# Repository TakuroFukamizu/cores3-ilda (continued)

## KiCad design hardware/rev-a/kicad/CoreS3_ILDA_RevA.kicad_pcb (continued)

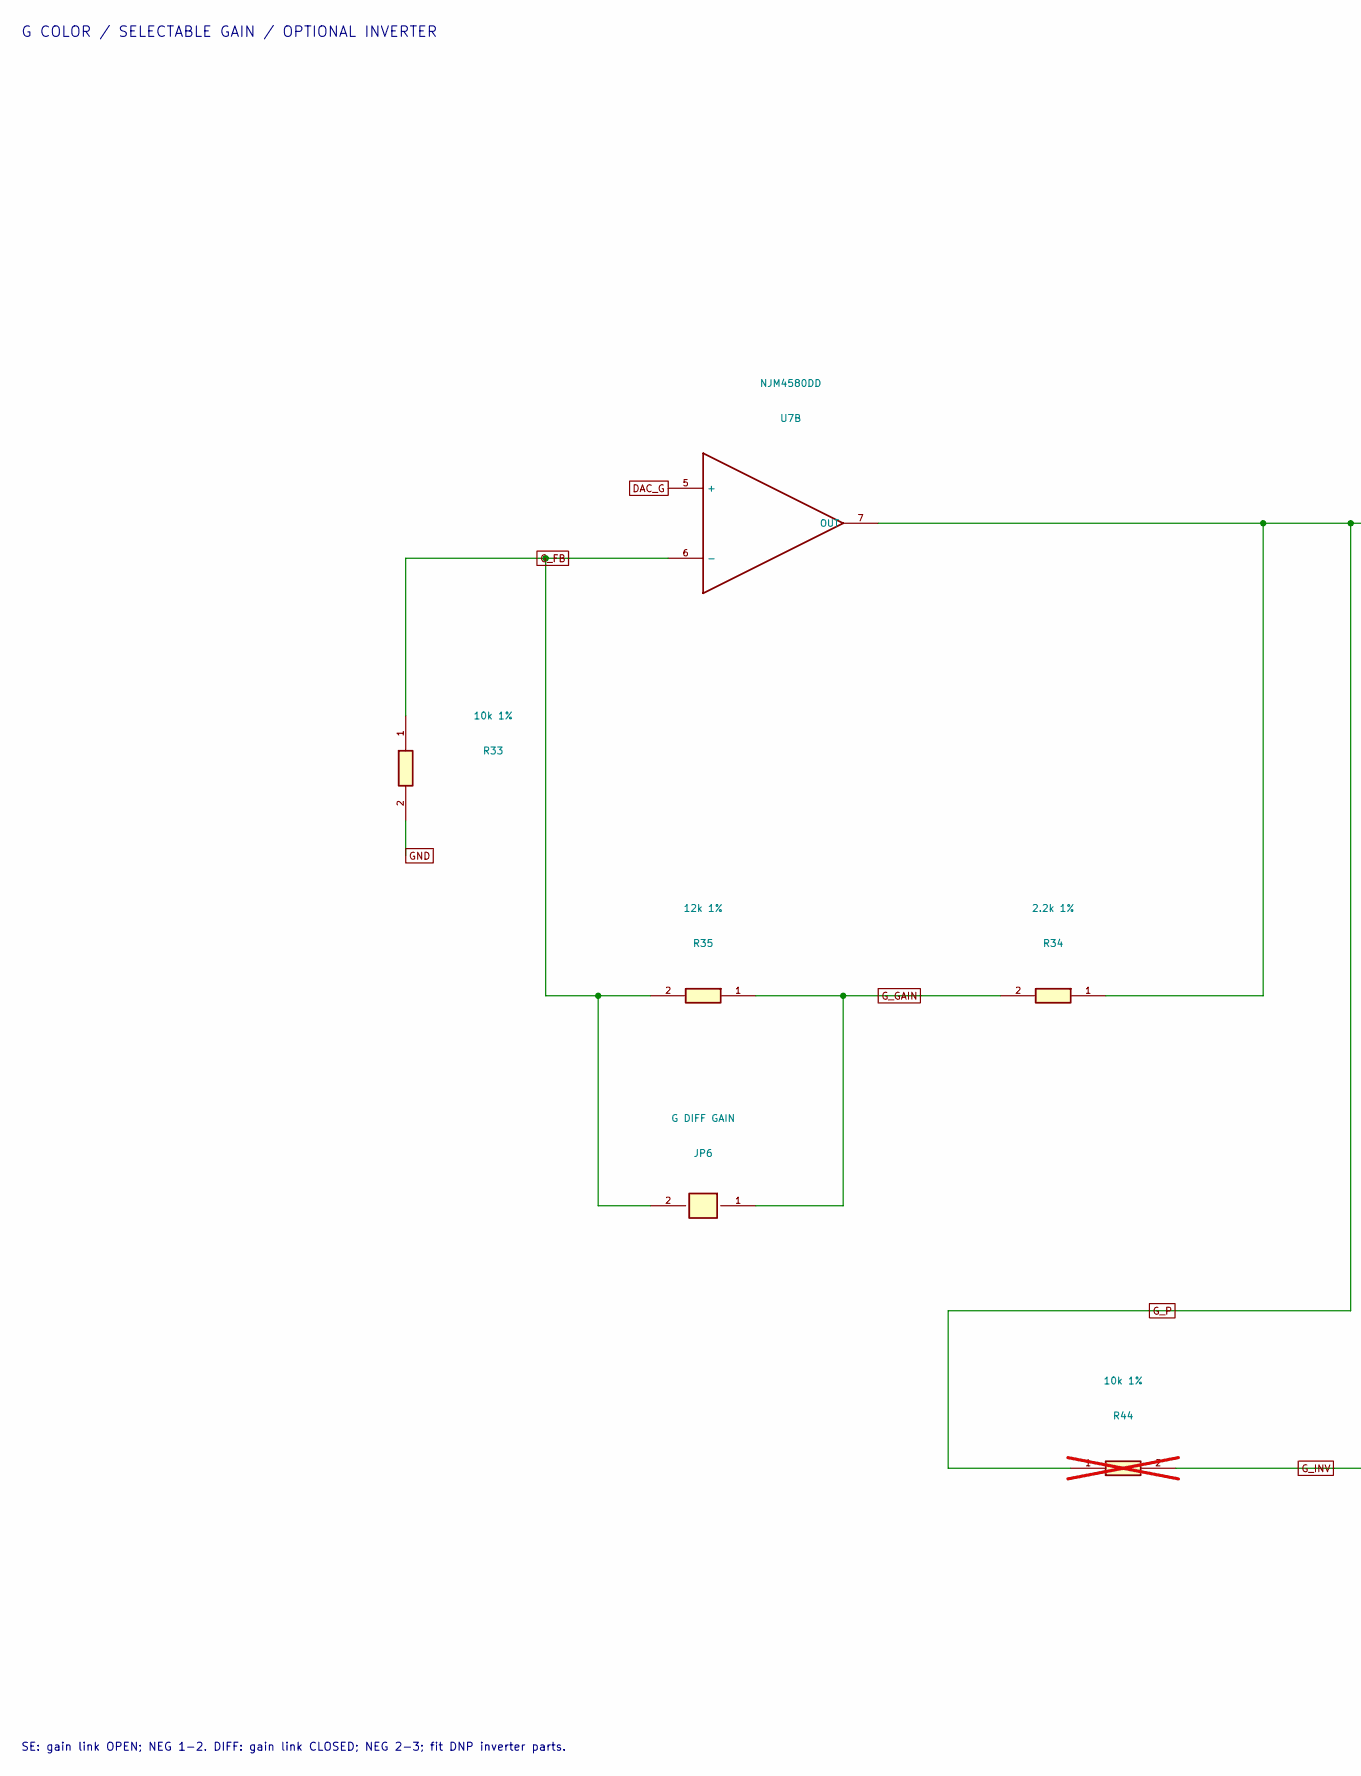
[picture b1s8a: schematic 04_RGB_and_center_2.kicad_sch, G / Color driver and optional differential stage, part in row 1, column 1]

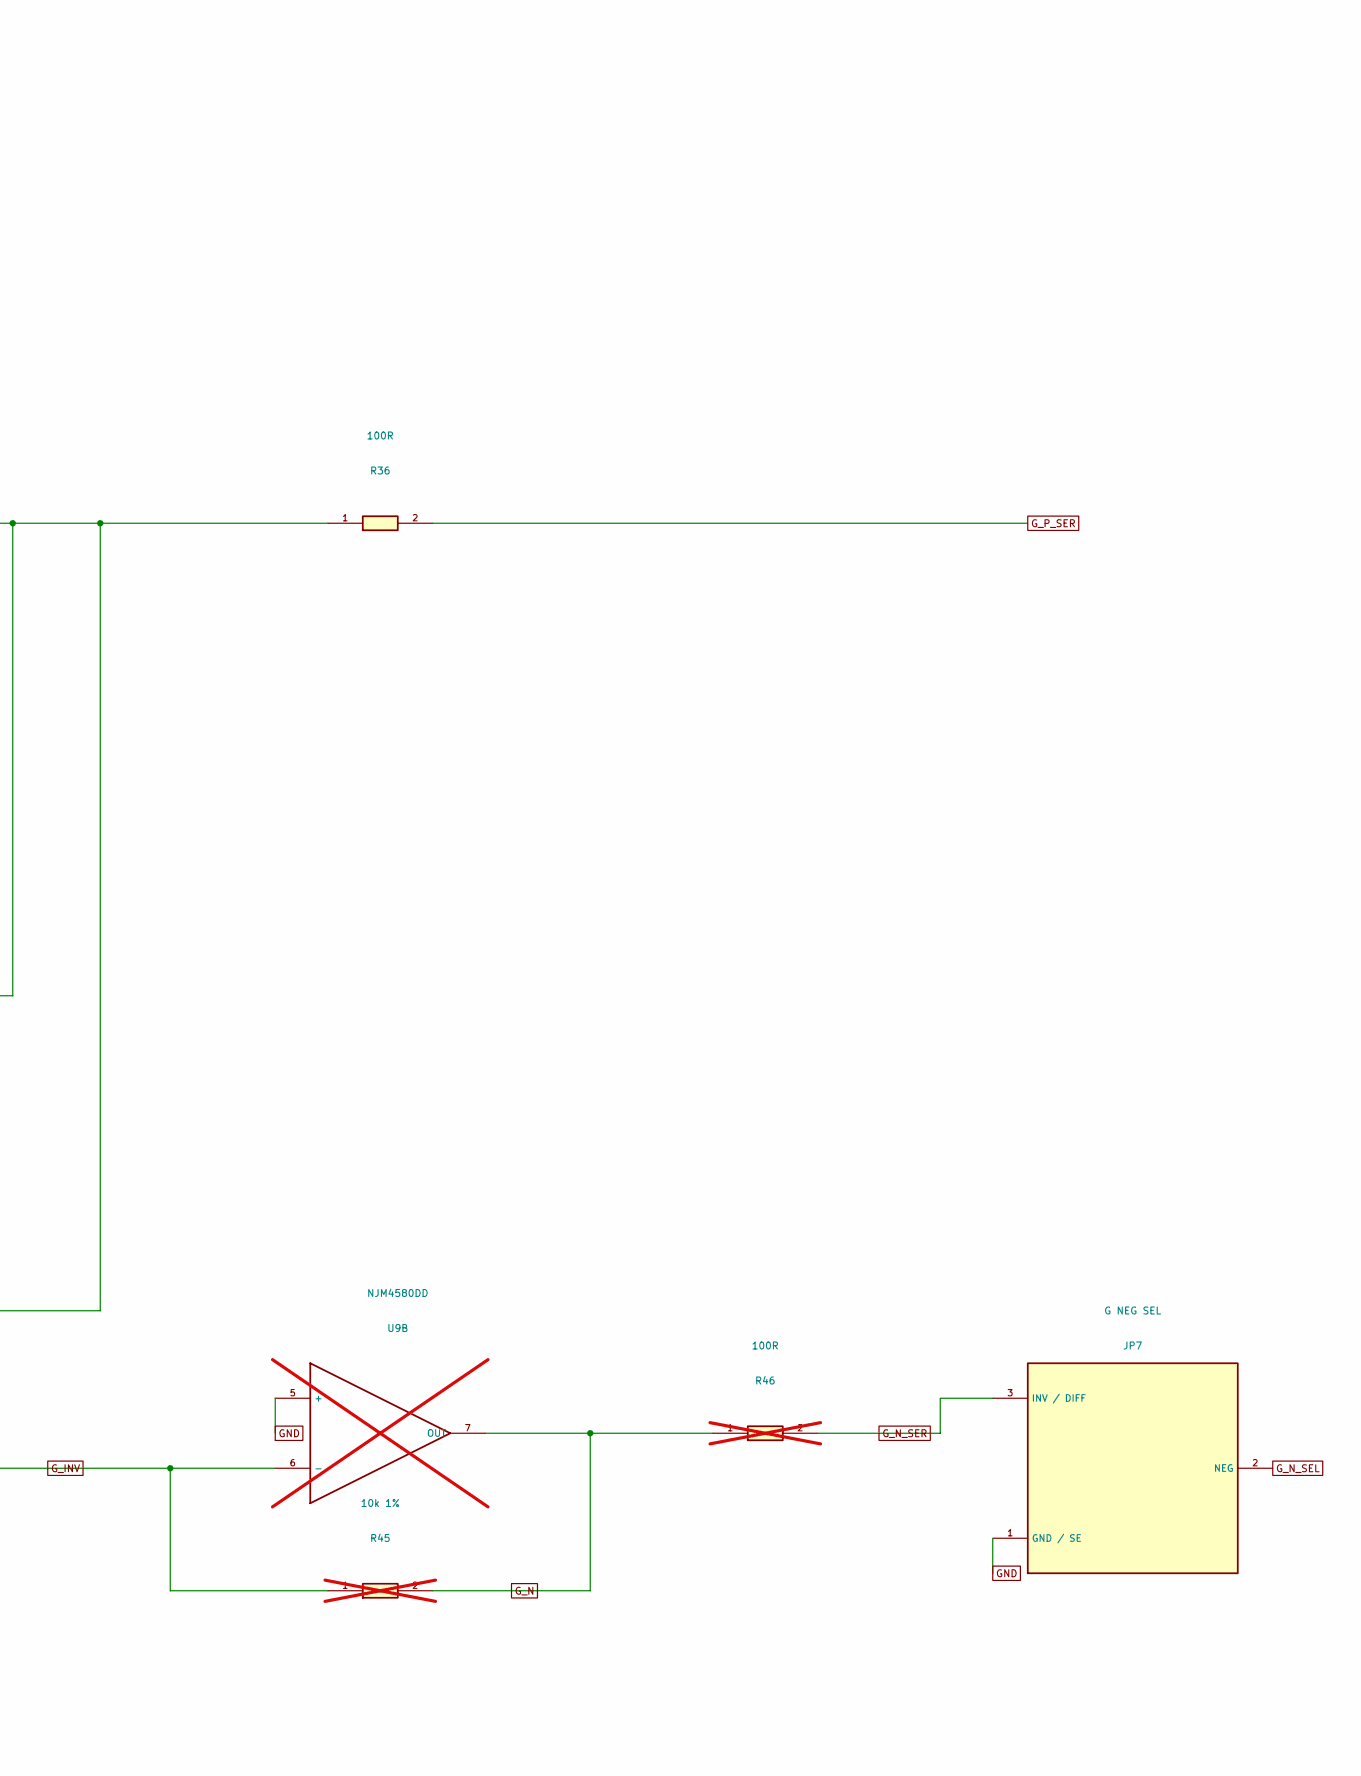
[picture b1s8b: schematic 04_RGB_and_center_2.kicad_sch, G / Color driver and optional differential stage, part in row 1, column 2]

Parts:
JP6: G DIFF GAIN; PinHeader_1x02_P2.54mm_Vertical
JP7: G NEG SEL; PinHeader_1x03_P2.54mm_Vertical
R33: 10k 1%; R_Axial_DIN0207_L6.3mm_D2.5mm_P10.16mm_Horizontal
R34: 2.2k 1%; R_Axial_DIN0207_L6.3mm_D2.5mm_P10.16mm_Horizontal
R35: 12k 1%; R_Axial_DIN0207_L6.3mm_D2.5mm_P10.16mm_Horizontal
R36: 100R; R_Axial_DIN0207_L6.3mm_D2.5mm_P10.16mm_Horizontal
R44, R45: 10k 1%; R_Axial_DIN0207_L6.3mm_D2.5mm_P10.16mm_Horizontal; not fitted
R46: 100R; R_Axial_DIN0207_L6.3mm_D2.5mm_P10.16mm_Horizontal; not fitted
U7: NJM4580DD; DIP-8_W7.62mm
U9: NJM4580DD; DIP-8_W7.62mm; not fitted

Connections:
DAC_G: U7.5 (+); also elsewhere on the board
GND: JP7.1 (GND / SE), R33.2, U9.5 (+); also elsewhere on the board
G_FB: JP6.2, R33.1, R35.2, U7.6 (-)
G_GAIN: JP6.1, R34.2, R35.1
G_INV: R44.2, R45.1, U9.6 (-)
G_N: R45.2, R46.1, U9.7 (OUT)
G_N_SEL: JP7.2 (NEG); also elsewhere on the board
G_N_SER: JP7.3 (INV / DIFF), R46.2
G_P: R34.1, R36.1, R44.1, U7.7 (OUT)
G_P_SER: R36.2; also elsewhere on the board

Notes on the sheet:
G COLOR / SELECTABLE GAIN / OPTIONAL INVERTER
SE: gain link OPEN; NEG 1-2. DIFF: gain link CLOSED; NEG 2-3; fit DNP inverter parts.

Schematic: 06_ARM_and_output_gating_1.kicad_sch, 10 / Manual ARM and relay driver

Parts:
D1: 1N4007; D_DO-41_SOD81_P10.16mm_Horizontal
J3: ARM external maintained NO; TerminalBlock_Phoenix_MKDS-1,5-2_1x02_P5.00mm_Horizontal
J4: E-STOP loop NC; TerminalBlock_Phoenix_MKDS-1,5-2_1x02_P5.00mm_Horizontal
Q1: IRLML6344TRPBF; SOT-23
R50: 100R; R_Axial_DIN0207_L6.3mm_D2.5mm_P10.16mm_Horizontal
R51: 10k; R_Axial_DIN0207_L6.3mm_D2.5mm_P10.16mm_Horizontal
TP26: COIL_5V; TestPoint_THTPad_D2.0mm_Drill1.0mm

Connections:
5V: J3.1; also elsewhere on the board
ARM_FEED: J3.2, J4.1
COIL_5V: D1.1, J4.2, TP26.1; also elsewhere on the board
COIL_LOW: D1.2, Q1.3 (D); also elsewhere on the board
ENABLE_GPIO: R50.1; also elsewhere on the board
EN_GATE: Q1.1 (G), R50.2, R51.1
GND: Q1.2 (S), R51.2; also elsewhere on the board

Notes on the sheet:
ARM + E-STOP + GPIO ENABLE
External maintained NO ARM switch; external NC emergency-stop loop.
GPIO high only after safe DAC initialization. Relays provide slow enable, not point blanking.

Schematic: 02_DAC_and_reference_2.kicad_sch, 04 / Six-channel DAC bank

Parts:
C9, C10, C11, C12, C13, C14: 100nF; C_Disc_D5.0mm_W2.5mm_P5.00mm
JP3: DAC RUN TEST; PinHeader_1x02_P2.54mm_Vertical
R10: 10k; R_Axial_DIN0207_L6.3mm_D2.5mm_P10.16mm_Horizontal
TP1: DAC_X; TestPoint_THTPad_D2.0mm_Drill1.0mm
TP2: DAC_Y; TestPoint_THTPad_D2.0mm_Drill1.0mm
TP3: DAC_R; TestPoint_THTPad_D2.0mm_Drill1.0mm
TP4: DAC_G; TestPoint_THTPad_D2.0mm_Drill1.0mm
TP5: DAC_B; TestPoint_THTPad_D2.0mm_Drill1.0mm
TP6: DAC_I; TestPoint_THTPad_D2.0mm_Drill1.0mm
U1, U2, U3: MCP4922-E/P; DIP-14_W7.62mm

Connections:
3V3: C9.1, C11.1, C13.1, R10.1, U1.1 (VDD), U2.1 (VDD), U3.1 (VDD); also elsewhere on the board
CS_BI_N: U3.3 (CS); also elsewhere on the board
CS_RG_N: U2.3 (CS); also elsewhere on the board
CS_XY_N: U1.3 (CS); also elsewhere on the board
DAC_B: TP5.1, U3.14 (OUT A); also elsewhere on the board
DAC_G: TP4.1, U2.10 (OUT B); also elsewhere on the board
DAC_I: TP6.1, U3.10 (OUT B); also elsewhere on the board
DAC_R: TP3.1, U2.14 (OUT A); also elsewhere on the board
DAC_RUN: JP3.1, R10.2, U1.9 (SHDN), U2.9 (SHDN), U3.9 (SHDN)
DAC_X: TP1.1, U1.14 (OUT A); also elsewhere on the board
DAC_Y: TP2.1, U1.10 (OUT B); also elsewhere on the board
GND: C9.2, C10.2, C11.2, C12.2, C13.2, C14.2, JP3.2, U1.12 (GND), U2.12 (GND), U3.12 (GND); also elsewhere on the board
LDAC_N: U1.8 (LDAC), U2.8 (LDAC), U3.8 (LDAC); also elsewhere on the board
MOSI: U1.5 (SDI), U2.5 (SDI), U3.5 (SDI); also elsewhere on the board
SCK: U1.4 (SCK), U2.4 (SCK), U3.4 (SCK); also elsewhere on the board
VREF_2V048: C10.1, C12.1, C14.1, U1.11 (VREFB), U1.13 (VREFA), U2.11 (VREFB), U2.13 (VREFA), U3.11 (VREFB), U3.13 (VREFA); also elsewhere on the board

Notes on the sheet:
6 DAC CHANNELS / COMMON LDAC
Common SCK / SDI / LDAC / SHDN are wired across all three DACs.
JP3 OPEN. SPI mode 0; BUF=0, GA=1, SHDN=1. Write 6 channels, then pulse LDAC.

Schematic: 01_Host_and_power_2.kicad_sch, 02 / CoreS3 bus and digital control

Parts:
J1: CoreS3 M5-Bus; M5Bus_CoreS3_TypeA
JP2: GPIO9 TEST; PinHeader_1x02_P2.54mm_Vertical
R3, R4: 33R; R_Axial_DIN0207_L6.3mm_D2.5mm_P10.16mm_Horizontal
R5, R6, R7, R8, R9: 10k; R_Axial_DIN0207_L6.3mm_D2.5mm_P10.16mm_Horizontal
TP21: 3V3; TestPoint_THTPad_D2.0mm_Drill1.0mm
TP25: ENABLE_GPIO; TestPoint_THTPad_D2.0mm_Drill1.0mm

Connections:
3V3: J1.12 (3V3), R5.1, R6.1, R7.1, R8.1, TP21.1; also elsewhere on the board
5V_BUS: J1.28 (5V); also elsewhere on the board
CS_BI_N: J1.22 (G7), R7.2; also elsewhere on the board
CS_RG_N: J1.21 (G6), R6.2; also elsewhere on the board
CS_XY_N: J1.8 (G5), R5.2; also elsewhere on the board
ENABLE_GPIO: J1.2 (G10), R9.1, TP25.1; also elsewhere on the board
G9_SPARE: J1.10 (G9), JP2.1
GND: J1.1 (GND), J1.3 (GND), J1.5 (GND), JP2.2, R9.2; also elsewhere on the board
LDAC_N: J1.4 (G8), R8.2; also elsewhere on the board
MOSI: R3.2; also elsewhere on the board
MOSI_HOST: J1.7 (G37), R3.1
SCK: R4.2; also elsewhere on the board
SCK_HOST: J1.11 (G36), R4.1

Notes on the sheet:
CORES3 SPI / CONTROL
G37 MOSI / G36 SCK. Shared LCD/SD SPI requires transaction arbitration.

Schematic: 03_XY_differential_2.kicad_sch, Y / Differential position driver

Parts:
R19, R21, R23, R24: 10k 1%; R_Axial_DIN0207_L6.3mm_D2.5mm_P10.16mm_Horizontal
R20, R22: 47k 1%; R_Axial_DIN0207_L6.3mm_D2.5mm_P10.16mm_Horizontal
R25, R26: 100R; R_Axial_DIN0207_L6.3mm_D2.5mm_P10.16mm_Horizontal
TP9: Y+; TestPoint_THTPad_D2.0mm_Drill1.0mm
TP10: Y-; TestPoint_THTPad_D2.0mm_Drill1.0mm
U6: NJM4580DD; DIP-8_W7.62mm

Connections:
DAC_Y: R21.1; also elsewhere on the board
GND: R22.2, U6.5 (+); also elsewhere on the board
VCENTER: R19.1; also elsewhere on the board
Y+: R25.2, TP9.1; also elsewhere on the board
Y-: R26.2, TP10.1; also elsewhere on the board
Y_DIV: R21.2, R22.1, U6.3 (+)
Y_FB: R19.2, R20.2, U6.2 (-)
Y_INV: R23.2, R24.1, U6.6 (-)
Y_N: R24.2, R26.1, U6.7 (OUT)
Y_P: R20.1, R23.1, R25.1, U6.1 (OUT)

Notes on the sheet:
Y POSITION / SUBTRACT CENTER / INVERT / OUTPUT
V+ = 4.7 x (VDAC - 1.024V); V- = -V+. Initialize DAC code to 2048.

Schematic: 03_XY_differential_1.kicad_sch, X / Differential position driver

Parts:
R11, R13, R15, R16: 10k 1%; R_Axial_DIN0207_L6.3mm_D2.5mm_P10.16mm_Horizontal
R12, R14: 47k 1%; R_Axial_DIN0207_L6.3mm_D2.5mm_P10.16mm_Horizontal
R17, R18: 100R; R_Axial_DIN0207_L6.3mm_D2.5mm_P10.16mm_Horizontal
TP7: X+; TestPoint_THTPad_D2.0mm_Drill1.0mm
TP8: X-; TestPoint_THTPad_D2.0mm_Drill1.0mm
U5: NJM4580DD; DIP-8_W7.62mm

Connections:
DAC_X: R13.1; also elsewhere on the board
GND: R14.2, U5.5 (+); also elsewhere on the board
VCENTER: R11.1; also elsewhere on the board
X+: R17.2, TP7.1; also elsewhere on the board
X-: R18.2, TP8.1; also elsewhere on the board
X_DIV: R13.2, R14.1, U5.3 (+)
X_FB: R11.2, R12.2, U5.2 (-)
X_INV: R15.2, R16.1, U5.6 (-)
X_N: R16.2, R18.1, U5.7 (OUT)
X_P: R12.1, R15.1, R17.1, U5.1 (OUT)

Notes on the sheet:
X POSITION / SUBTRACT CENTER / INVERT / OUTPUT
V+ = 4.7 x (VDAC - 1.024V); V- = -V+. Initialize DAC code to 2048.

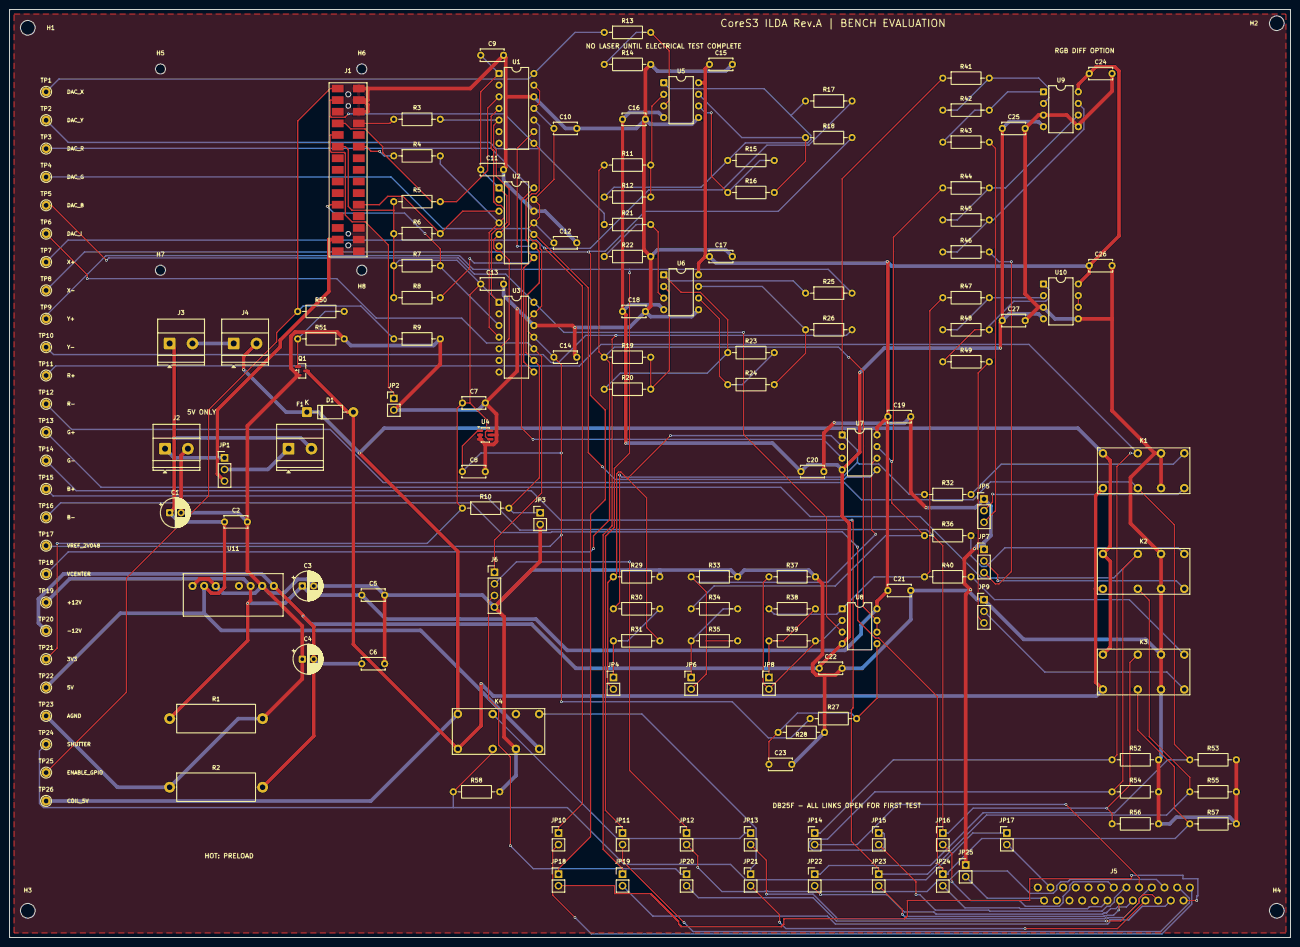
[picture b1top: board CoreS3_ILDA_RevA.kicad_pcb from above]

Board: 2 copper layers, 280.0 x 202.8 mm, 168 parts (0 on the bottom side), 98 nets.

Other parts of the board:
H1, H2, H3, H4: MountingHole_3.2mm_M3
H5, H6, H7, H8: MountingHole_2.2mm_M2

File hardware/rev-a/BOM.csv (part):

Reference,Value,Quantity,Population,Footprint,Akizuki_code,URL,Notes
J1,CoreS3 M5-Bus,1,FIT,RevA:M5Bus_CoreS3_TypeA,,https://shop.m5stack.com/products/2-%E2%9C%96-15-pinheader-b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,M5Stack A117 SMD Bus Socket 13.2 procurement candidate; check actual mating/mechanical fit. Official CoreS3 Type-A SMT geometry; not generic THT.
J2,5V external 2A,1,FIT,"RevA:TerminalBlock_Phoenix_MKDS-1,5-2_1x02_P5.00mm_Horizontal",,,
JP1,5V SOURCE,1,FIT,RevA:PinHeader_1x03_P2.54mm_Vertical,,,1-2 EXT (default); 2-3 BUS only after verifying CoreS3 5V budget. NEVER both.
F1,T2A external fuse,1,FIT,"RevA:TerminalBlock_Phoenix_MKDS-1,5-2_1x02_P5.00mm_Horizontal",,,Connect external insulated inline fuse holder with 2A slow-blow fuse between these terminals; no wire bypass.
U11,MCW03-05D12,1,FIT,RevA:MCW03_SIP8,104265,https://akizukidenshi.com/catalog/g/g104265/,
C1,100uF/16V,1,FIT,RevA:CP_Radial_D6.3mm_P2.50mm,,,16V minimum; 25V acceptable if diameter 6.3mm / pitch 2.5mm fits.
C2,100nF,1,FIT,RevA:C_Disc_D5.0mm_W2.5mm_P5.00mm,,,50V X7R/C0G
C3,22uF/25V,1,FIT,RevA:CP_Radial_D6.3mm_P2.50mm,,,25V minimum
C4,22uF/25V,1,FIT,RevA:CP_Radial_D6.3mm_P2.50mm,,,25V minimum
C5,100nF,1,FIT,RevA:C_Disc_D5.0mm_W2.5mm_P5.00mm,,,50V X7R/C0G
C6,100nF,1,FIT,RevA:C_Disc_D5.0mm_W2.5mm_P5.00mm,,,50V X7R/C0G
R1,330R 2W,1,FIT,RevA:R_Axial_DIN0617_L17.0mm_D6.0mm_P20.32mm_Horizontal,,,"Minimum load 36mA, 0.44W at 12V; mount 5mm above board"
R2,330R 2W,1,FIT,RevA:R_Axial_DIN0617_L17.0mm_D6.0mm_P20.32mm_Horizontal,,,Minimum load 36mA; keep away from voltage reference
R3,33R,1,FIT,RevA:R_Axial_DIN0207_L6.3mm_D2.5mm_P10.16mm_Horizontal,,,
R4,33R,1,FIT,RevA:R_Axial_DIN0207_L6.3mm_D2.5mm_P10.16mm_Horizontal,,,
R5,10k,1,FIT,RevA:R_Axial_DIN0207_L6.3mm_D2.5mm_P10.16mm_Horizontal,,,
R6,10k,1,FIT,RevA:R_Axial_DIN0207_L6.3mm_D2.5mm_P10.16mm_Horizontal,,,
R7,10k,1,FIT,RevA:R_Axial_DIN0207_L6.3mm_D2.5mm_P10.16mm_Horizontal,,,
R8,10k,1,FIT,RevA:R_Axial_DIN0207_L6.3mm_D2.5mm_P10.16mm_Horizontal,,,
R9,10k,1,FIT,RevA:R_Axial_DIN0207_L6.3mm_D2.5mm_P10.16mm_Horizontal,,,
JP2,GPIO9 TEST,1,FIT,RevA:PinHeader_1x02_P2.54mm_Vertical,,,
U4,MCP1501-20E/CHY,1,FIT,RevA:SOT-23-6,115203,https://akizukidenshi.com/catalog/g/g115203/,
C7,100nF,1,FIT,RevA:C_Disc_D5.0mm_W2.5mm_P5.00mm,,,50V X7R/C0G
C8,1uF,1,FIT,RevA:C_Disc_D5.0mm_W2.5mm_P5.00mm,,,50V X7R/C0G
U1,MCP4922-E/P,1,FIT,RevA:DIP-14_W7.62mm,102090,https://akizukidenshi.com/catalog/g/g102090/,
C9,100nF,1,FIT,RevA:C_Disc_D5.0mm_W2.5mm_P5.00mm,,,50V X7R/C0G
C10,100nF,1,FIT,RevA:C_Disc_D5.0mm_W2.5mm_P5.00mm,,,50V X7R/C0G
TP1,DAC_X,1,FIT,RevA:TestPoint_THTPad_D2.0mm_Drill1.0mm,,,
TP2,DAC_Y,1,FIT,RevA:TestPoint_THTPad_D2.0mm_Drill1.0mm,,,
U2,MCP4922-E/P,1,FIT,RevA:DIP-14_W7.62mm,102090,https://akizukidenshi.com/catalog/g/g102090/,
C11,100nF,1,FIT,RevA:C_Disc_D5.0mm_W2.5mm_P5.00mm,,,50V X7R/C0G
C12,100nF,1,FIT,RevA:C_Disc_D5.0mm_W2.5mm_P5.00mm,,,50V X7R/C0G
TP3,DAC_R,1,FIT,RevA:TestPoint_THTPad_D2.0mm_Drill1.0mm,,,
TP4,DAC_G,1,FIT,RevA:TestPoint_THTPad_D2.0mm_Drill1.0mm,,,
U3,MCP4922-E/P,1,FIT,RevA:DIP-14_W7.62mm,102090,https://akizukidenshi.com/catalog/g/g102090/,
C13,100nF,1,FIT,RevA:C_Disc_D5.0mm_W2.5mm_P5.00mm,,,50V X7R/C0G
C14,100nF,1,FIT,RevA:C_Disc_D5.0mm_W2.5mm_P5.00mm,,,50V X7R/C0G
TP5,DAC_B,1,FIT,RevA:TestPoint_THTPad_D2.0mm_Drill1.0mm,,,
TP6,DAC_I,1,FIT,RevA:TestPoint_THTPad_D2.0mm_Drill1.0mm,,,
R10,10k,1,FIT,RevA:R_Axial_DIN0207_L6.3mm_D2.5mm_P10.16mm_Horizontal,,,
JP3,DAC RUN TEST,1,FIT,RevA:PinHeader_1x02_P2.54mm_Vertical,,,"Open = RUN; shunt disables ALL DACs. XY goes to a rail, NOT center."
U5,NJM4580DD,1,FIT,RevA:DIP-8_W7.62mm,100069,https://akizukidenshi.com/catalog/g/g100069/,
C15,100nF,1,FIT,RevA:C_Disc_D5.0mm_W2.5mm_P5.00mm,,,50V X7R/C0G
C16,100nF,1,FIT,RevA:C_Disc_D5.0mm_W2.5mm_P5.00mm,,,50V X7R/C0G
R11,10k 1%,1,FIT,RevA:R_Axial_DIN0207_L6.3mm_D2.5mm_P10.16mm_Horizontal,,,
R12,47k 1%,1,FIT,RevA:R_Axial_DIN0207_L6.3mm_D2.5mm_P10.16mm_Horizontal,,,
R13,10k 1%,1,FIT,RevA:R_Axial_DIN0207_L6.3mm_D2.5mm_P10.16mm_Horizontal,,,
R14,47k 1%,1,FIT,RevA:R_Axial_DIN0207_L6.3mm_D2.5mm_P10.16mm_Horizontal,,,
R15,10k 1%,1,FIT,RevA:R_Axial_DIN0207_L6.3mm_D2.5mm_P10.16mm_Horizontal,,,
R16,10k 1%,1,FIT,RevA:R_Axial_DIN0207_L6.3mm_D2.5mm_P10.16mm_Horizontal,,,
R17,100R,1,FIT,RevA:R_Axial_DIN0207_L6.3mm_D2.5mm_P10.16mm_Horizontal,,,
R18,100R,1,FIT,RevA:R_Axial_DIN0207_L6.3mm_D2.5mm_P10.16mm_Horizontal,,,
U6,NJM4580DD,1,FIT,RevA:DIP-8_W7.62mm,100069,https://akizukidenshi.com/catalog/g/g100069/,
C17,100nF,1,FIT,RevA:C_Disc_D5.0mm_W2.5mm_P5.00mm,,,50V X7R/C0G
C18,100nF,1,FIT,RevA:C_Disc_D5.0mm_W2.5mm_P5.00mm,,,50V X7R/C0G
R19,10k 1%,1,FIT,RevA:R_Axial_DIN0207_L6.3mm_D2.5mm_P10.16mm_Horizontal,,,
R20,47k 1%,1,FIT,RevA:R_Axial_DIN0207_L6.3mm_D2.5mm_P10.16mm_Horizontal,,,
R21,10k 1%,1,FIT,RevA:R_Axial_DIN0207_L6.3mm_D2.5mm_P10.16mm_Horizontal,,,
R22,47k 1%,1,FIT,RevA:R_Axial_DIN0207_L6.3mm_D2.5mm_P10.16mm_Horizontal,,,
R23,10k 1%,1,FIT,RevA:R_Axial_DIN0207_L6.3mm_D2.5mm_P10.16mm_Horizontal,,,
R24,10k 1%,1,FIT,RevA:R_Axial_DIN0207_L6.3mm_D2.5mm_P10.16mm_Horizontal,,,
R25,100R,1,FIT,RevA:R_Axial_DIN0207_L6.3mm_D2.5mm_P10.16mm_Horizontal,,,
R26,100R,1,FIT,RevA:R_Axial_DIN0207_L6.3mm_D2.5mm_P10.16mm_Horizontal,,,
U7,NJM4580DD,1,FIT,RevA:DIP-8_W7.62mm,100069,https://akizukidenshi.com/catalog/g/g100069/,
C19,100nF,1,FIT,RevA:C_Disc_D5.0mm_W2.5mm_P5.00mm,,,50V X7R/C0G
C20,100nF,1,FIT,RevA:C_Disc_D5.0mm_W2.5mm_P5.00mm,,,50V X7R/C0G
U8,NJM4580DD,1,FIT,RevA:DIP-8_W7.62mm,100069,https://akizukidenshi.com/catalog/g/g100069/,
C21,100nF,1,FIT,RevA:C_Disc_D5.0mm_W2.5mm_P5.00mm,,,50V X7R/C0G
C22,100nF,1,FIT,RevA:C_Disc_D5.0mm_W2.5mm_P5.00mm,,,50V X7R/C0G
R27,10k 1%,1,FIT,RevA:R_Axial_DIN0207_L6.3mm_D2.5mm_P10.16mm_Horizontal,,,
R28,10k 1%,1,FIT,RevA:R_Axial_DIN0207_L6.3mm_D2.5mm_P10.16mm_Horizontal,,,
C23,1uF,1,FIT,RevA:C_Disc_D5.0mm_W2.5mm_P5.00mm,,,50V X7R/C0G
R29,10k 1%,1,FIT,RevA:R_Axial_DIN0207_L6.3mm_D2.5mm_P10.16mm_Horizontal,,,
R30,2.2k 1%,1,FIT,RevA:R_Axial_DIN0207_L6.3mm_D2.5mm_P10.16mm_Horizontal,,,
R31,12k 1%,1,FIT,RevA:R_Axial_DIN0207_L6.3mm_D2.5mm_P10.16mm_Horizontal,,,
JP4,R DIFF GAIN,1,FIT,RevA:PinHeader_1x02_P2.54mm_Vertical,,,OPEN: SE gain2.42. CLOSED: DIFF gain1.22; fit optional inverter and change NEG selector.
R32,100R,1,FIT,RevA:R_Axial_DIN0207_L6.3mm_D2.5mm_P10.16mm_Horizontal,,,
JP5,R NEG SEL,1,FIT,RevA:PinHeader_1x03_P2.54mm_Vertical,,,1-2 SE default; 2-3 DIFF needs gain jumper + optional inverter.
R33,10k 1%,1,FIT,RevA:R_Axial_DIN0207_L6.3mm_D2.5mm_P10.16mm_Horizontal,,,
R34,2.2k 1%,1,FIT,RevA:R_Axial_DIN0207_L6.3mm_D2.5mm_P10.16mm_Horizontal,,,
R35,12k 1%,1,FIT,RevA:R_Axial_DIN0207_L6.3mm_D2.5mm_P10.16mm_Horizontal,,,
JP6,G DIFF GAIN,1,FIT,RevA:PinHeader_1x02_P2.54mm_Vertical,,,OPEN: SE gain2.42. CLOSED: DIFF gain1.22; fit optional inverter and change NEG selector.
R36,100R,1,FIT,RevA:R_Axial_DIN0207_L6.3mm_D2.5mm_P10.16mm_Horizontal,,,
JP7,G NEG SEL,1,FIT,RevA:PinHeader_1x03_P2.54mm_Vertical,,,1-2 SE default; 2-3 DIFF needs gain jumper + optional inverter.
R37,10k 1%,1,FIT,RevA:R_Axial_DIN0207_L6.3mm_D2.5mm_P10.16mm_Horizontal,,,
R38,2.2k 1%,1,FIT,RevA:R_Axial_DIN0207_L6.3mm_D2.5mm_P10.16mm_Horizontal,,,
R39,12k 1%,1,FIT,RevA:R_Axial_DIN0207_L6.3mm_D2.5mm_P10.16mm_Horizontal,,,
JP8,B DIFF GAIN,1,FIT,RevA:PinHeader_1x02_P2.54mm_Vertical,,,OPEN: SE gain2.42. CLOSED: DIFF gain1.22; fit optional inverter and change NEG selector.
R40,100R,1,FIT,RevA:R_Axial_DIN0207_L6.3mm_D2.5mm_P10.16mm_Horizontal,,,
JP9,B NEG SEL,1,FIT,RevA:PinHeader_1x03_P2.54mm_Vertical,,,1-2 SE default; 2-3 DIFF needs gain jumper + optional inverter.
U9,NJM4580DD,1,DNP optional,RevA:DIP-8_W7.62mm,100069,https://akizukidenshi.com/catalog/g/g100069/,
C24,100nF,1,DNP optional,RevA:C_Disc_D5.0mm_W2.5mm_P5.00mm,,,50V X7R/C0G
C25,100nF,1,DNP optional,RevA:C_Disc_D5.0mm_W2.5mm_P5.00mm,,,50V X7R/C0G
U10,NJM4580DD,1,DNP optional,RevA:DIP-8_W7.62mm,100069,https://akizukidenshi.com/catalog/g/g100069/,
C26,100nF,1,DNP optional,RevA:C_Disc_D5.0mm_W2.5mm_P5.00mm,,,50V X7R/C0G
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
